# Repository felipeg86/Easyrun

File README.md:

# Easyrun :bike:

Sistema de automatización de préstamo de bicicletas dentro del campus de la Universidad Nacional de Colombia, incorporando la conexión entre estaciones y facilitando el proceso que a la fecha se implementa. El sistema tiene como objetivo principal, reducir los tiempos en el uso del servicio, especialmente en los puntos de prestámo y entrega, además de permitir un control sobre la trazabilidad de cada bicicleta.

Integrantes: 

* Ana Milena Espinosa Jiménez
* Laura Valentina Moreno Castro
* Johan Stevens Higuera Espinel
* Omar Andrés Cely Villate
* Juan Felipe González Pardo
* Kishvari Osorio Delgado
* Johan Sebastian Molina Martinez

## Organización del repositorio

El proyecto se organiza en las sigueintes carpetas:

> * En la carpeta "[Circuit Design](https://github.com/felipeg86/Easyrun/tree/main/Circuit%20Design)" se encuentran las simulaciones, diseños y esquemáticos llevados a cabo en el diseño del hardware del sistema.
> * "[Micropython](https://github.com/felipeg86/Easyrun/tree/main/Micropython)" contiene los scripts utilizados para programar el microcontrolador de la solución.
> * En "[Case Design](https://github.com/felipeg86/Easyrun/tree/main/Case%20Design)" se encuentran los modelos 3D, planos y consideraciones físicas para la cubierta y componentes mecánicos. 
> * "[Budget](https://github.com/felipeg86/Easyrun/tree/main/Budget)" contiene el presupuesto detallado para el desarrollo del prototipo. 
> * "[Imágenes](https://github.com/felipeg86/Easyrun/tree/main/Images)" almacena las imágenes utilizadas en la documentación y en los archivos readme de cada sección.

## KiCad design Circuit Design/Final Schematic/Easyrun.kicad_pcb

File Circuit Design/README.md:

## Organización de la carpeta
### En "[Datasheets](https://github.com/felipeg86/Easyrun/tree/main/Circuit%20Design/Datasheets)" se presentan las hojas de datos y especificaciones de algunos de los componentes de hardware utilizados en la solución.
### "[LTspice Simulations](https://github.com/felipeg86/Easyrun/tree/main/Circuit%20Design/LTspice%20Simulations)" contiene las simulaciones realizadas para el diseño y validación de algunos de los subsistemas.
### "[Final Schematic](https://github.com/felipeg86/Easyrun/tree/main/Circuit%20Design/Final%20Schematic)" almacena los archivos de diseño y fabricación de la placa de circuito impreso del sistema.

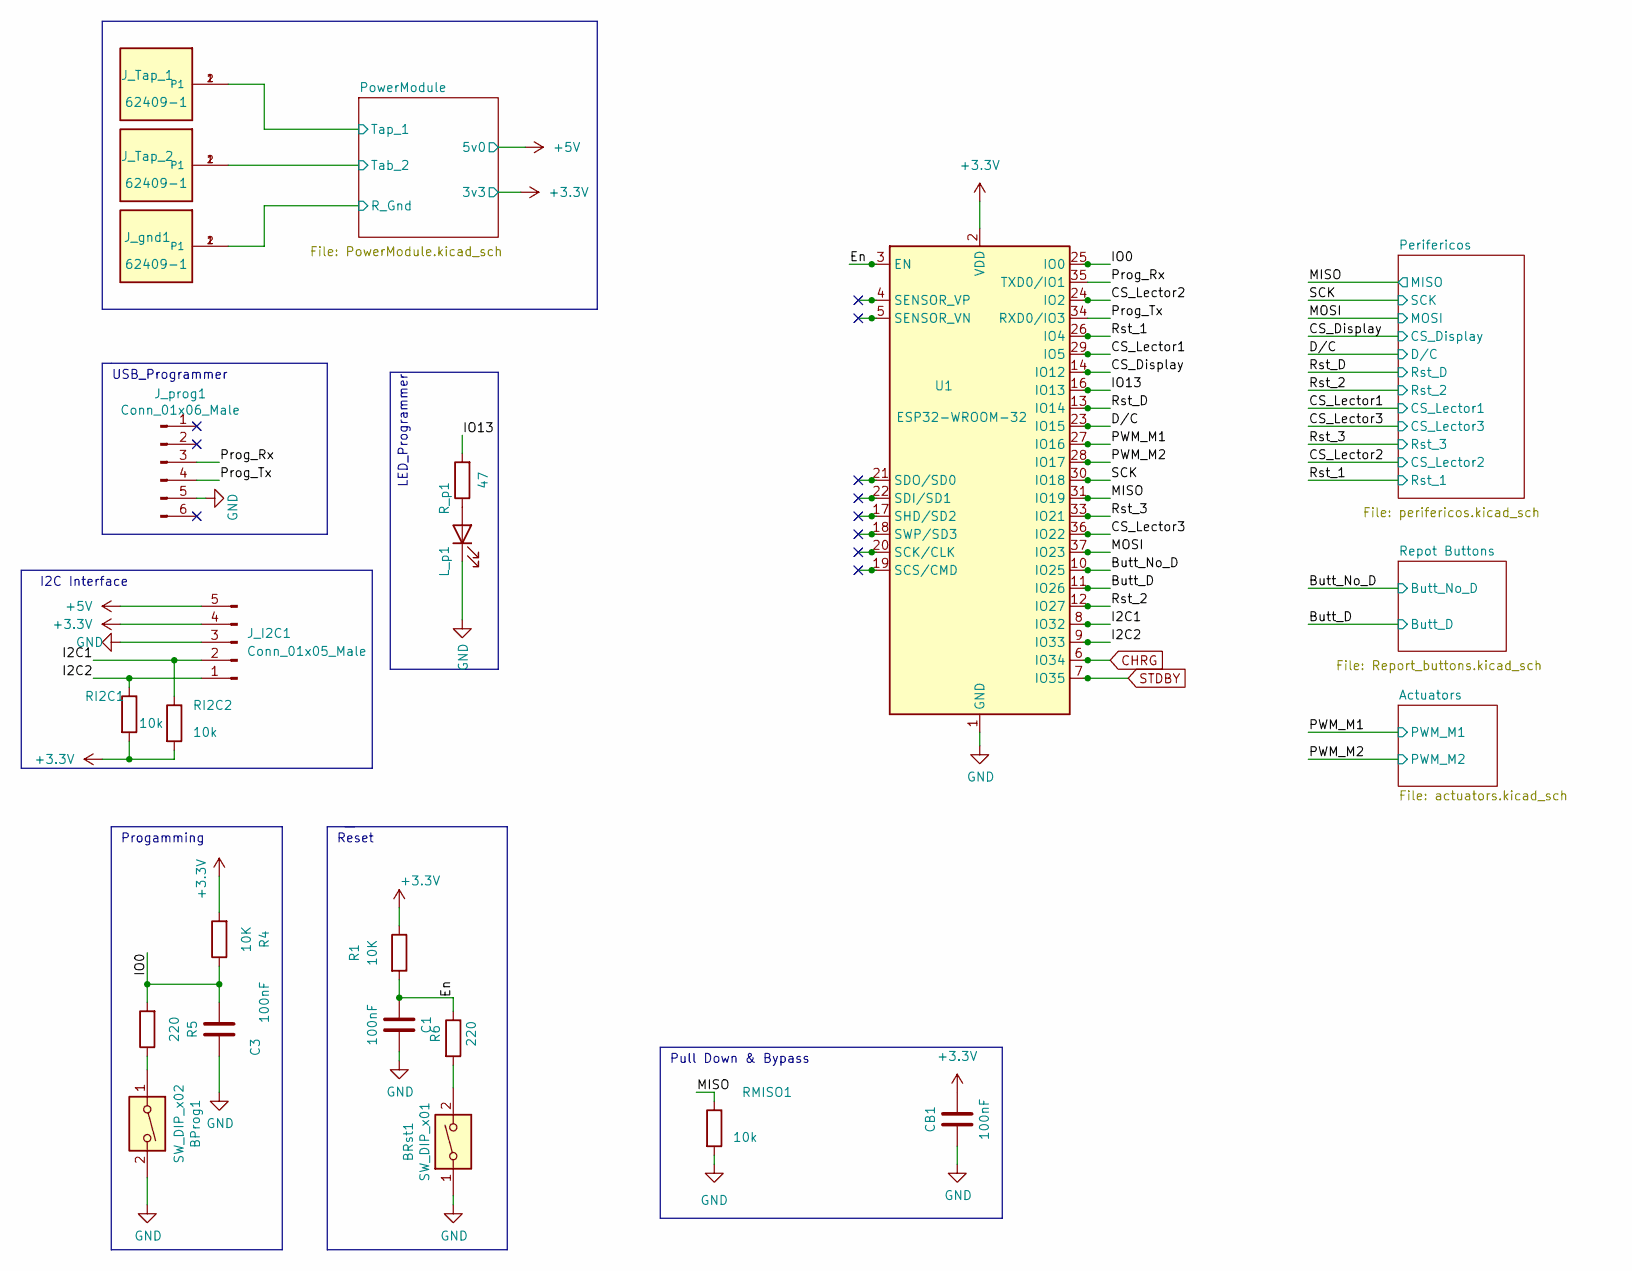
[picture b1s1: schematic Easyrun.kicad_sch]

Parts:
BProg1: SW_DIP_x02; SW_SPST_CK_RS282G05A3
BRst1: SW_DIP_x01; SW_SPST_CK_RS282G05A3
C1, C3: 100nF; C_0805_2012Metric_Pad1.18x1.45mm_HandSolder
CB1: 100nF; C_0805_2012Metric_Pad1.18x1.45mm_HandSolder
J_I2C1: Conn_01x05_Male; PinSocket_1x05_P2.54mm_Horizontal
J_Tap_1, J_Tap_2: 62409-1; TE_62409-1
J_gnd1: 62409-1; TE_62409-1
J_prog1: Conn_01x06_Male; PinHeader_1x06_P2.54mm_Horizontal
L_p1: LED; LED_0805_2012Metric_Pad1.15x1.40mm_HandSolder
R1, R4: 10K; R_0805_2012Metric_Pad1.20x1.40mm_HandSolder
R5, R6: 220; R_0805_2012Metric_Pad1.20x1.40mm_HandSolder
RI2C1, RI2C2: 10k; R_0805_2012Metric_Pad1.20x1.40mm_HandSolder
RMISO1: 10k; R_0805_2012Metric_Pad1.20x1.40mm_HandSolder
R_p1: 47; R_0805_2012Metric_Pad1.20x1.40mm_HandSolder
U1: ESP32-WROOM-32

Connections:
+3V3: CB1.1, J_I2C1.4, R1.1, R4.2, RI2C1.2, RI2C2.2, U1.2 (VDD); also elsewhere on the board
+5V: J_I2C1.5; also elsewhere on the board
/Butt_D: U1.11 (IO26); also elsewhere on the board
/Butt_No_D: U1.10 (IO25); also elsewhere on the board
/CS_Display: U1.14 (IO12); also elsewhere on the board
/CS_Lector1: U1.29 (IO5); also elsewhere on the board
/CS_Lector2: U1.24 (IO2); also elsewhere on the board
/CS_Lector3: U1.36 (IO22); also elsewhere on the board
/D/C: U1.23 (IO15); also elsewhere on the board
/En: C1.2, R1.2, R6.1, U1.3 (EN)
/I2C1: J_I2C1.2, RI2C2.1, U1.8 (IO32)
/I2C2: J_I2C1.1, RI2C1.1, U1.9 (IO33)
/IO0: C3.1, R4.1, R5.2, U1.25 (IO0)
/IO13: R_p1.2, U1.16 (IO13)
/MISO: RMISO1.1, U1.31 (IO19); also elsewhere on the board
/MOSI: U1.37 (IO23); also elsewhere on the board
/PWM_M1: U1.27 (IO16); also elsewhere on the board
/PWM_M2: U1.28 (IO17); also elsewhere on the board
/PowerModule/R_Gnd: J_gnd1.1, J_gnd1.2 (P1); also elsewhere on the board
/PowerModule/Tab_2: J_Tap_2.1, J_Tap_2.2 (P1); also elsewhere on the board
/PowerModule/Tap_1: J_Tap_1.1, J_Tap_1.2 (P1); also elsewhere on the board
/Prog_Rx: J_prog1.3, U1.35 (TXD0/IO1)
/Prog_Tx: J_prog1.4, U1.34 (RXD0/IO3)
/Rst_1: U1.26 (IO4); also elsewhere on the board
/Rst_2: U1.12 (IO27); also elsewhere on the board
/Rst_3: U1.33 (IO21); also elsewhere on the board
/Rst_D: U1.13 (IO14); also elsewhere on the board
/SCK: U1.30 (IO18); also elsewhere on the board
CHRG: U1.6 (IO34); also elsewhere on the board
GND: BProg1.2, BRst1.1, C1.1, C3.2, CB1.2, J_I2C1.3, J_prog1.5, L_p1.1 (K), RMISO1.2, U1.1 (GND), U1.15 (GND), U1.38 (GND), U1.39 (GND); also elsewhere on the board
unnamed: BProg1.1, R5.1
unnamed: BRst1.2, R6.2
unnamed: L_p1.2 (A), R_p1.1
STDBY: U1.7 (IO35); also elsewhere on the board

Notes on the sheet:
LED_Programmer
I2C Interface
Progamming
Pull Down & Bypass
Reset
USB_Programmer

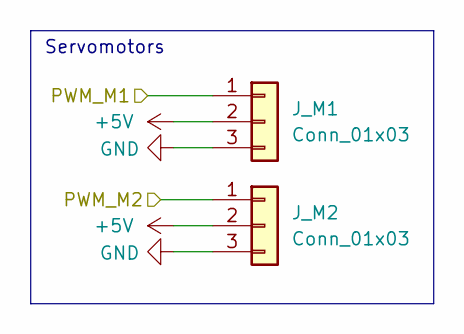
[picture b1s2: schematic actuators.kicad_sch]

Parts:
J_M1, J_M2: Conn_01x03; JST_EH_S3B-EH_1x03_P2.50mm_Horizontal

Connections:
+5V: J_M1.2, J_M2.2; also elsewhere on the board
/PWM_M1: J_M1.1; also elsewhere on the board
/PWM_M2: J_M2.1; also elsewhere on the board
GND: J_M1.3, J_M2.3; also elsewhere on the board

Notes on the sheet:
Servomotors

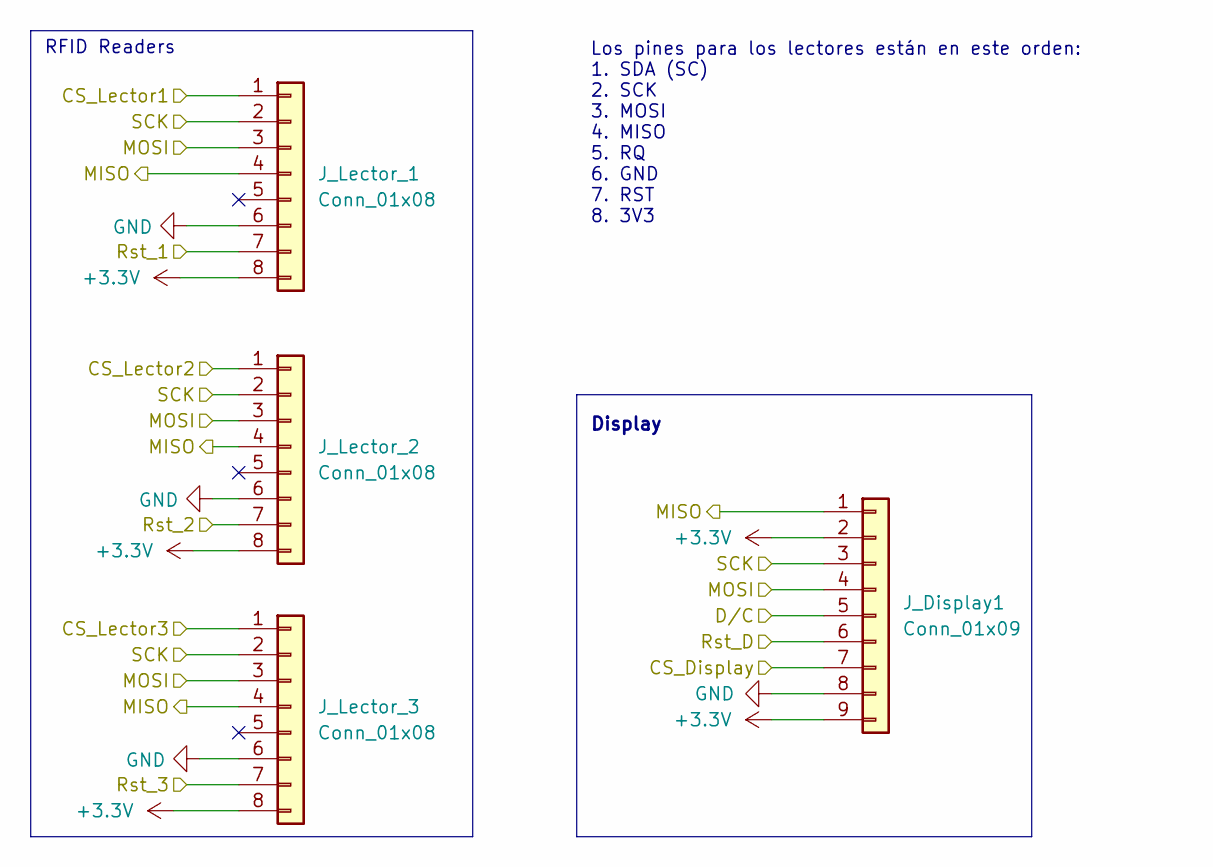
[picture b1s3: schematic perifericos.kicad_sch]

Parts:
J_Display1: Conn_01x09; JST_EH_S9B-EH_1x09_P2.50mm_Horizontal
J_Lector_1, J_Lector_2, J_Lector_3: Conn_01x08; JST_EH_S8B-EH_1x08_P2.50mm_Horizontal

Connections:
+3V3: J_Display1.2, J_Display1.9, J_Lector_1.8, J_Lector_2.8, J_Lector_3.8; also elsewhere on the board
/CS_Display: J_Display1.7; also elsewhere on the board
/CS_Lector1: J_Lector_1.1; also elsewhere on the board
/CS_Lector2: J_Lector_2.1; also elsewhere on the board
/CS_Lector3: J_Lector_3.1; also elsewhere on the board
/D/C: J_Display1.5; also elsewhere on the board
/MISO: J_Display1.1, J_Lector_1.4, J_Lector_2.4, J_Lector_3.4; also elsewhere on the board
/MOSI: J_Display1.4, J_Lector_1.3, J_Lector_2.3, J_Lector_3.3; also elsewhere on the board
/Rst_1: J_Lector_1.7; also elsewhere on the board
/Rst_2: J_Lector_2.7; also elsewhere on the board
/Rst_3: J_Lector_3.7; also elsewhere on the board
/Rst_D: J_Display1.6; also elsewhere on the board
/SCK: J_Display1.3, J_Lector_1.2, J_Lector_2.2, J_Lector_3.2; also elsewhere on the board
GND: J_Display1.8, J_Lector_1.6, J_Lector_2.6, J_Lector_3.6; also elsewhere on the board

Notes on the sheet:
RFID Readers
Display
Los pines para los lectores están en este orden: 1. SDA (SC) 2. SCK 3. MOSI 4. MISO 5. RQ 6. GND 7. RST 8. 3V3

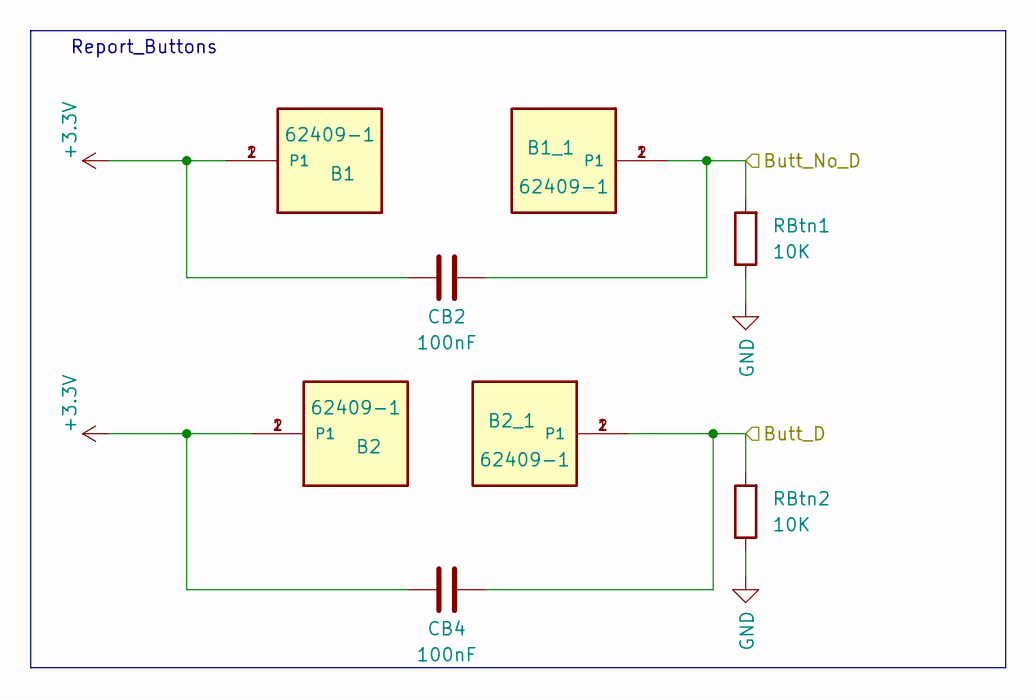
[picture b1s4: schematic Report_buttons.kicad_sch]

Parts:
B1, B1_1, B2, B2_1: 62409-1; TE_62409-1
CB2, CB4: 100nF; C_0805_2012Metric_Pad1.18x1.45mm_HandSolder
RBtn1, RBtn2: 10K; R_0805_2012Metric_Pad1.20x1.40mm_HandSolder

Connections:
+3V3: B1.1, B1.2 (P1), B2.1, B2.2 (P1), CB2.1, CB4.1; also elsewhere on the board
/Butt_D: B2_1.1, B2_1.2 (P1), CB4.2, RBtn2.2; also elsewhere on the board
/Butt_No_D: B1_1.1, B1_1.2 (P1), CB2.2, RBtn1.2; also elsewhere on the board
GND: RBtn1.1, RBtn2.1; also elsewhere on the board

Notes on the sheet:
Report_Buttons

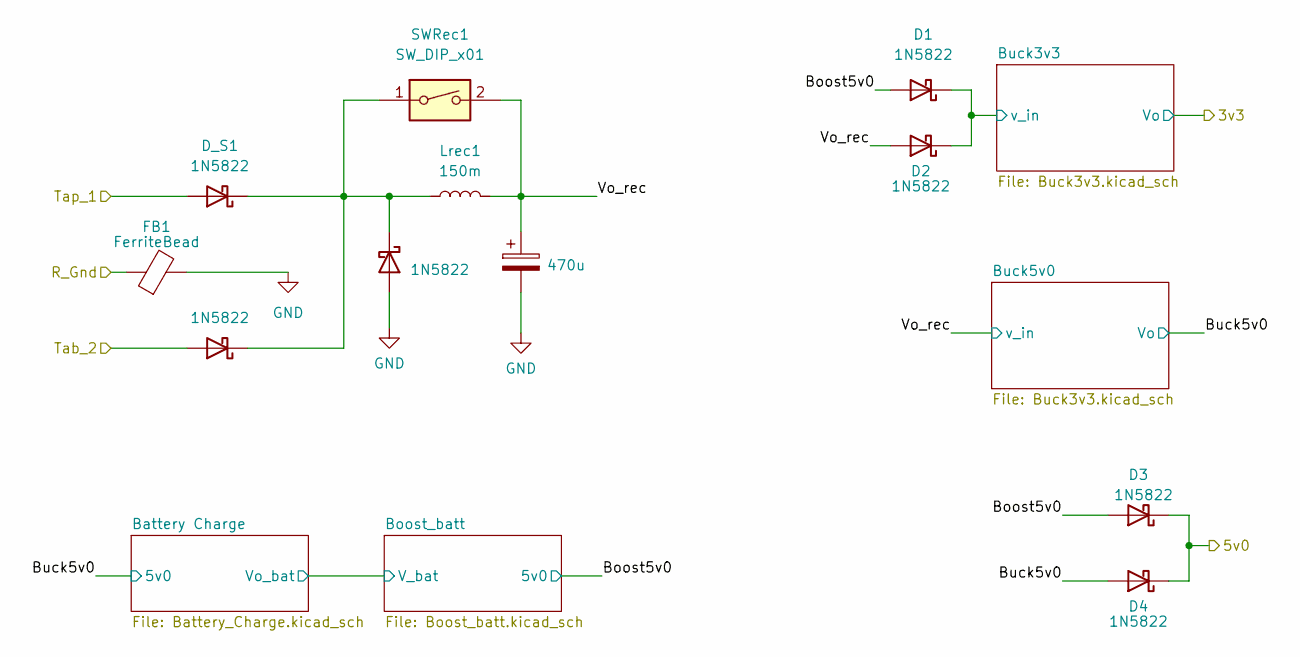
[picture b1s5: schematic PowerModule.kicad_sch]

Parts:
Crec1: 470u; CP_Radial_D6.3mm_P2.50mm
D1, D2, D3, D4: 1N5822; D_DO-201AE_P5.08mm_Vertical_AnodeUp
DFly1: 1N5822; D_DO-201AE_P5.08mm_Vertical_AnodeUp
D_S1, D_S2: 1N5822; D_DO-201AE_P5.08mm_Vertical_AnodeUp
FB1: FerriteBead; R_1812_4532Metric_Pad1.30x3.40mm_HandSolder
Lrec1: 150m; L_Toroid_Vertical_L25.4mm_W14.7mm_P12.20mm_Vishay_TJ5_BigPa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
SWRec1: SW_DIP_x01; PinHeader_1x02_P2.54mm_Vertical_SMD_Pin1Left

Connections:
+5V: D3.1 (K), D4.1 (K); also elsewhere on the board
/PowerModule/Boost5v0: D1.2 (A), D3.2 (A); also elsewhere on the board
/PowerModule/Buck3v3/v_in: D1.1 (K), D2.1 (K); also elsewhere on the board
/PowerModule/Buck5v0: D4.2 (A); also elsewhere on the board
/PowerModule/R_Gnd: FB1.1; also elsewhere on the board
/PowerModule/Tab_2: D_S2.2 (A); also elsewhere on the board
/PowerModule/Tap_1: D_S1.2 (A); also elsewhere on the board
/PowerModule/Vo_rec: Crec1.1, D2.2 (A), Lrec1.2, SWRec1.2; also elsewhere on the board
GND: Crec1.2, DFly1.2 (A), FB1.2; also elsewhere on the board
unnamed: DFly1.1 (K), D_S1.1 (K), D_S2.1 (K), Lrec1.1, SWRec1.1

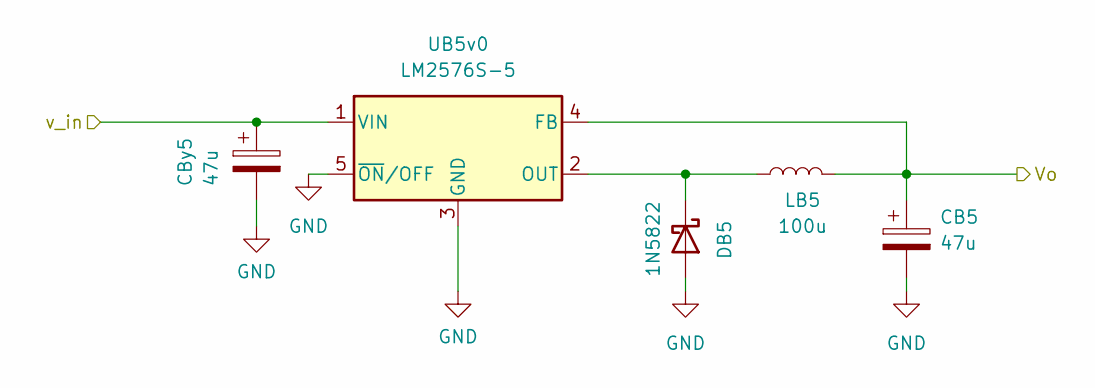
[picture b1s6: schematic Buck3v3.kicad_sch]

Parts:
CB5: 47u; CP_Elec_6.3x5.8
CBy5: 47u; CP_EIA-7343-43_Kemet-X_Pad2.25x2.55mm_HandSolder
DB5: 1N5822; D_DO-201AE_P5.08mm_Vertical_AnodeUp
LB5: 100u; L_Toroid_Vertical_L25.4mm_W14.7mm_P12.20mm_Vishay_TJ5_BigPa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
UB5v0: LM2576S-5; TO-263-5_TabPin3

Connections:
/PowerModule/Buck5v0: CB5.1, LB5.2, UB5v0.4 (FB); also elsewhere on the board
/PowerModule/Vo_rec: CBy5.1, UB5v0.1 (VIN); also elsewhere on the board
GND: CB5.2, CBy5.2, DB5.2 (A), UB5v0.3 (GND), UB5v0.5 (~ON/OFF); also elsewhere on the board
unnamed: DB5.1 (K), LB5.1, UB5v0.2 (OUT)

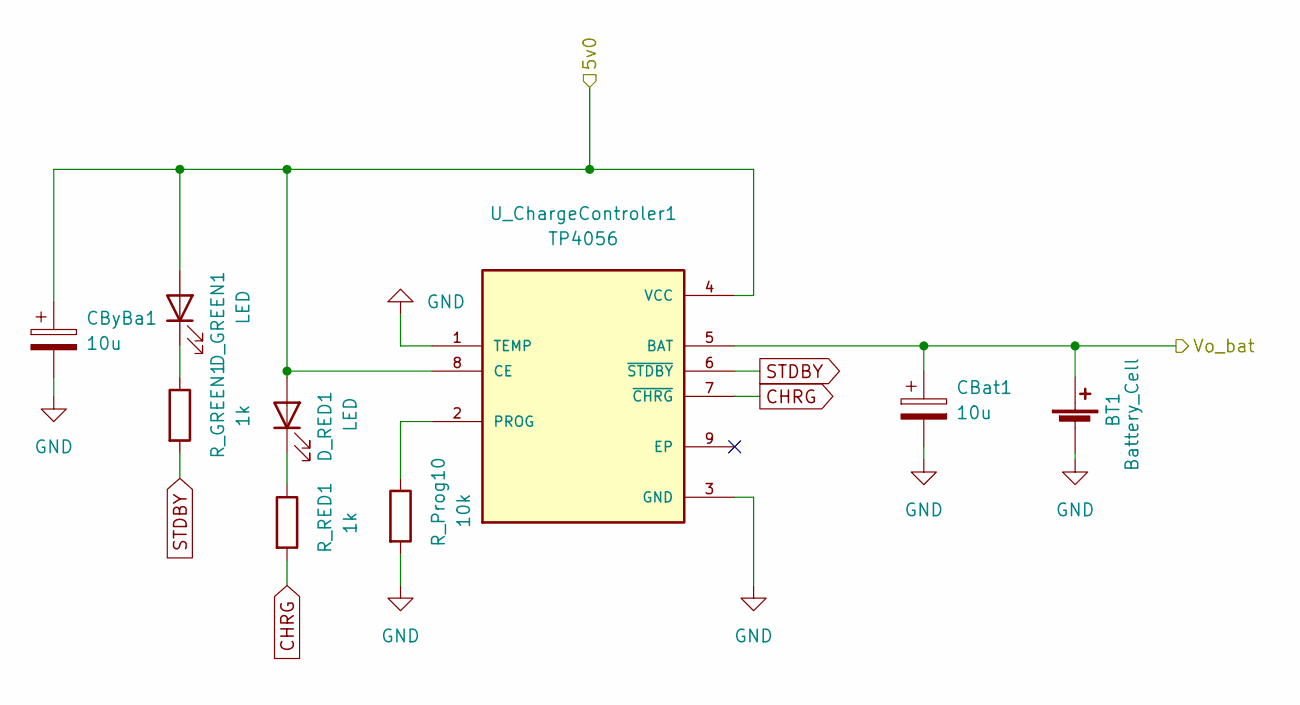
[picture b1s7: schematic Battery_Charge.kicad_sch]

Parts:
BT1: Battery_Cell; BatteryHolder_MPD_BH-18650-PC2
CBat1: 10u; CP_Elec_6.3x5.8
CByBa1: 10u; CP_Elec_6.3x5.8
D_GREEN1: LED; LED_0805_2012Metric_Pad1.15x1.40mm_HandSolder
D_RED1: LED; LED_0805_2012Metric_Pad1.15x1.40mm_HandSolder
R_GREEN1: 1k; R_0805_2012Metric_Pad1.20x1.40mm_HandSolder
R_Prog10: 10k; R_0805_2012Metric_Pad1.20x1.40mm_HandSolder
R_RED1: 1k; R_0805_2012Metric_Pad1.20x1.40mm_HandSolder
U_ChargeControler1: TP4056; SOP127P600X175-9N

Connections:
/PowerModule/Battery Charge/Vo_bat: BT1.1 (+), CBat1.1, U_ChargeControler1.5 (BAT); also elsewhere on the board
/PowerModule/Buck5v0: CByBa1.1, D_GREEN1.2 (A), D_RED1.2 (A), U_ChargeControler1.4 (VCC), U_ChargeControler1.8 (CE); also elsewhere on the board
CHRG: R_RED1.2, U_ChargeControler1.7 (~CHRG); also elsewhere on the board
GND: BT1.2 (-), CBat1.2, CByBa1.2, R_Prog10.2, U_ChargeControler1.1 (TEMP), U_ChargeControler1.3 (GND); also elsewhere on the board
unnamed: D_GREEN1.1 (K), R_GREEN1.1
unnamed: D_RED1.1 (K), R_RED1.1
unnamed: R_Prog10.1, U_ChargeControler1.2 (PROG)
STDBY: R_GREEN1.2, U_ChargeControler1.6 (~STDBY); also elsewhere on the board

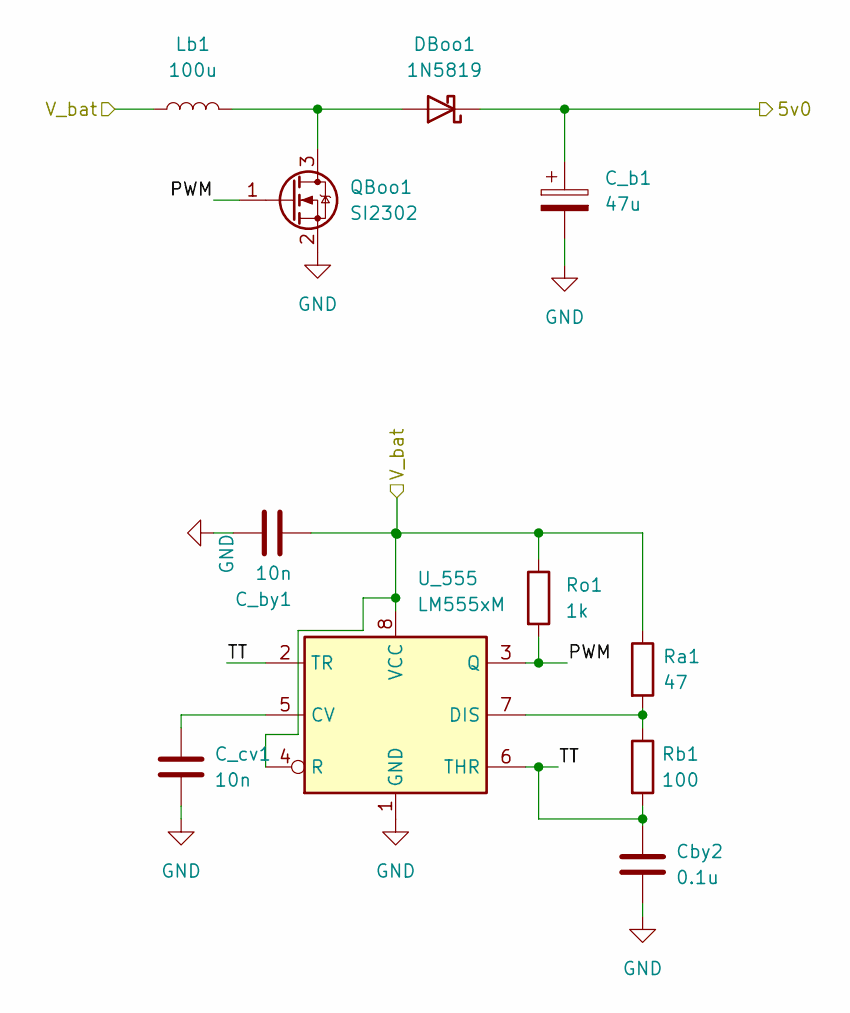
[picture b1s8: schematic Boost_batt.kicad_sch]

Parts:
C_b1: 47u; CP_Elec_6.3x5.8
C_by1: 10n; C_0805_2012Metric_Pad1.18x1.45mm_HandSolder
C_cv1: 10n; C_0805_2012Metric_Pad1.18x1.45mm_HandSolder
Cby2: 0.1u; C_0805_2012Metric_Pad1.18x1.45mm_HandSolder
DBoo1: 1N5819; D_DO-201AE_P5.08mm_Vertical_AnodeUp
Lb1: 100u; L_Toroid_Vertical_L25.4mm_W14.7mm_P12.20mm_Vishay_TJ5_BigPa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
QBoo1: SI2302; SOT-23
Ra1: 47; R_0805_2012Metric_Pad1.20x1.40mm_HandSolder
Rb1: 100; R_0805_2012Metric_Pad1.20x1.40mm_HandSolder
Ro1: 1k; R_0805_2012Metric_Pad1.20x1.40mm_HandSolder
U_555: LM555xM; SOIC-8_3.9x4.9mm_P1.27mm

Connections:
/PowerModule/Battery Charge/Vo_bat: Lb1.1; also elsewhere on the board
/PowerModule/Boost5v0: C_b1.1, DBoo1.1 (K); also elsewhere on the board
/PowerModule/Boost_batt/PWM: QBoo1.1 (G), Ro1.2, U_555.3 (Q)
/PowerModule/Boost_batt/TT: Cby2.1, Rb1.2, U_555.2 (TR), U_555.6 (THR)
GND: C_b1.2, C_by1.1, C_cv1.2, Cby2.2, QBoo1.2 (S), U_555.1 (GND); also elsewhere on the board
unnamed: C_by1.2, Ra1.1, Ro1.1, U_555.4 (R), U_555.8 (VCC)
unnamed: C_cv1.1, U_555.5 (CV)
unnamed: DBoo1.2 (A), Lb1.2, QBoo1.3 (D)
unnamed: Ra1.2, Rb1.1, U_555.7 (DIS)

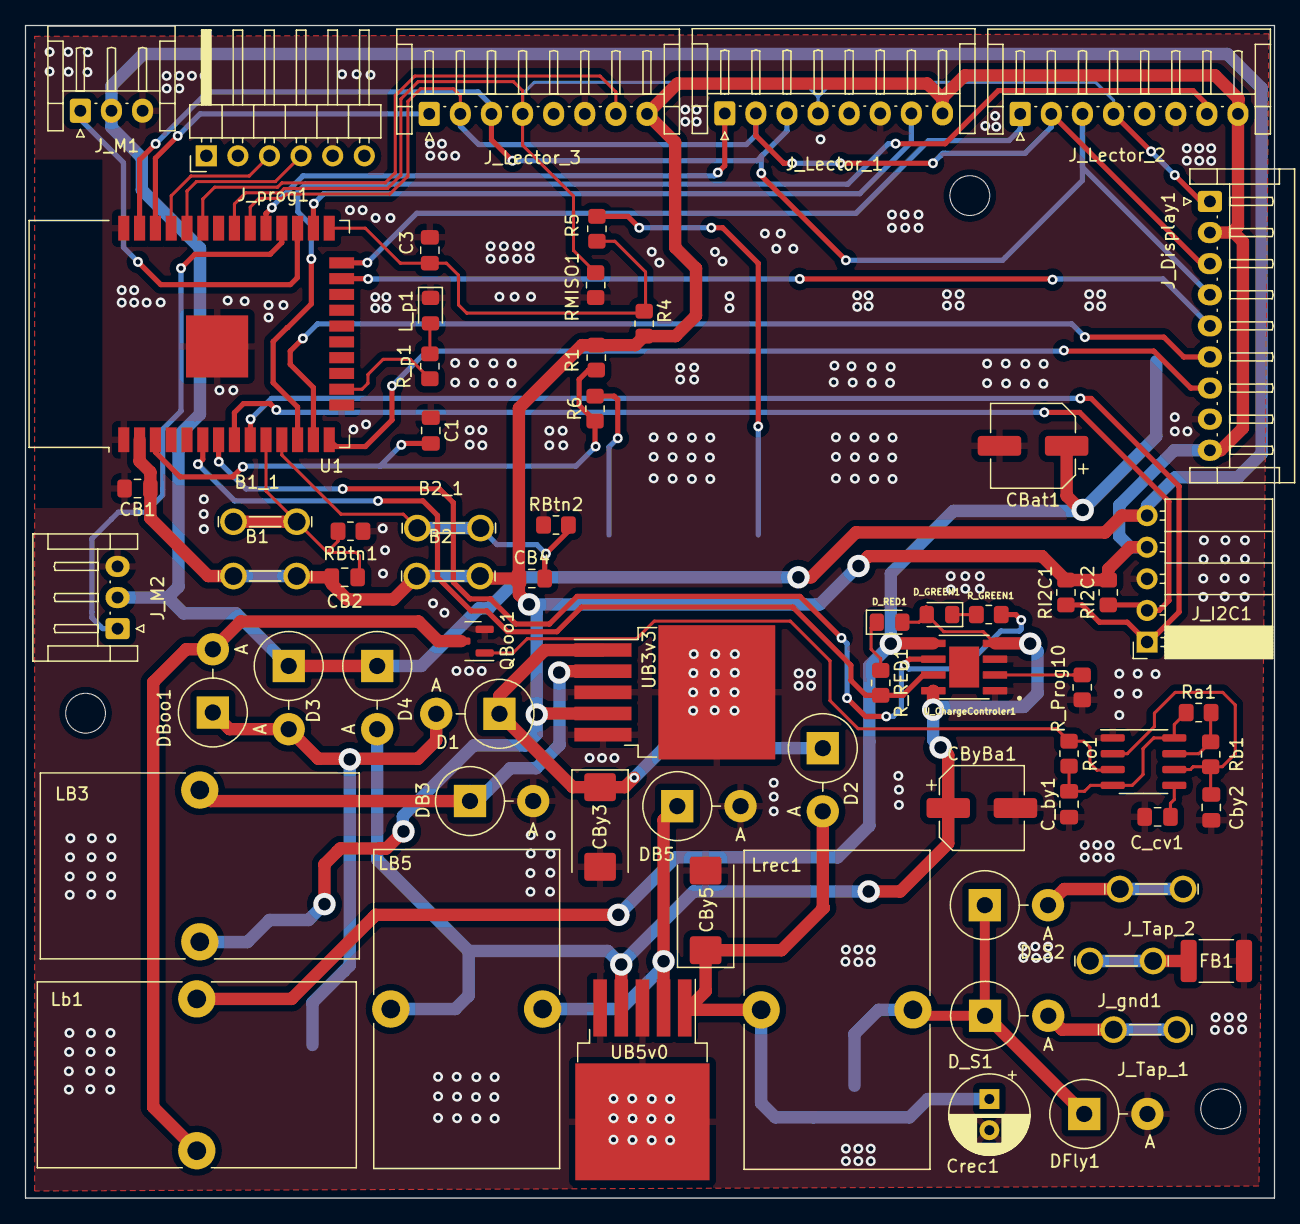
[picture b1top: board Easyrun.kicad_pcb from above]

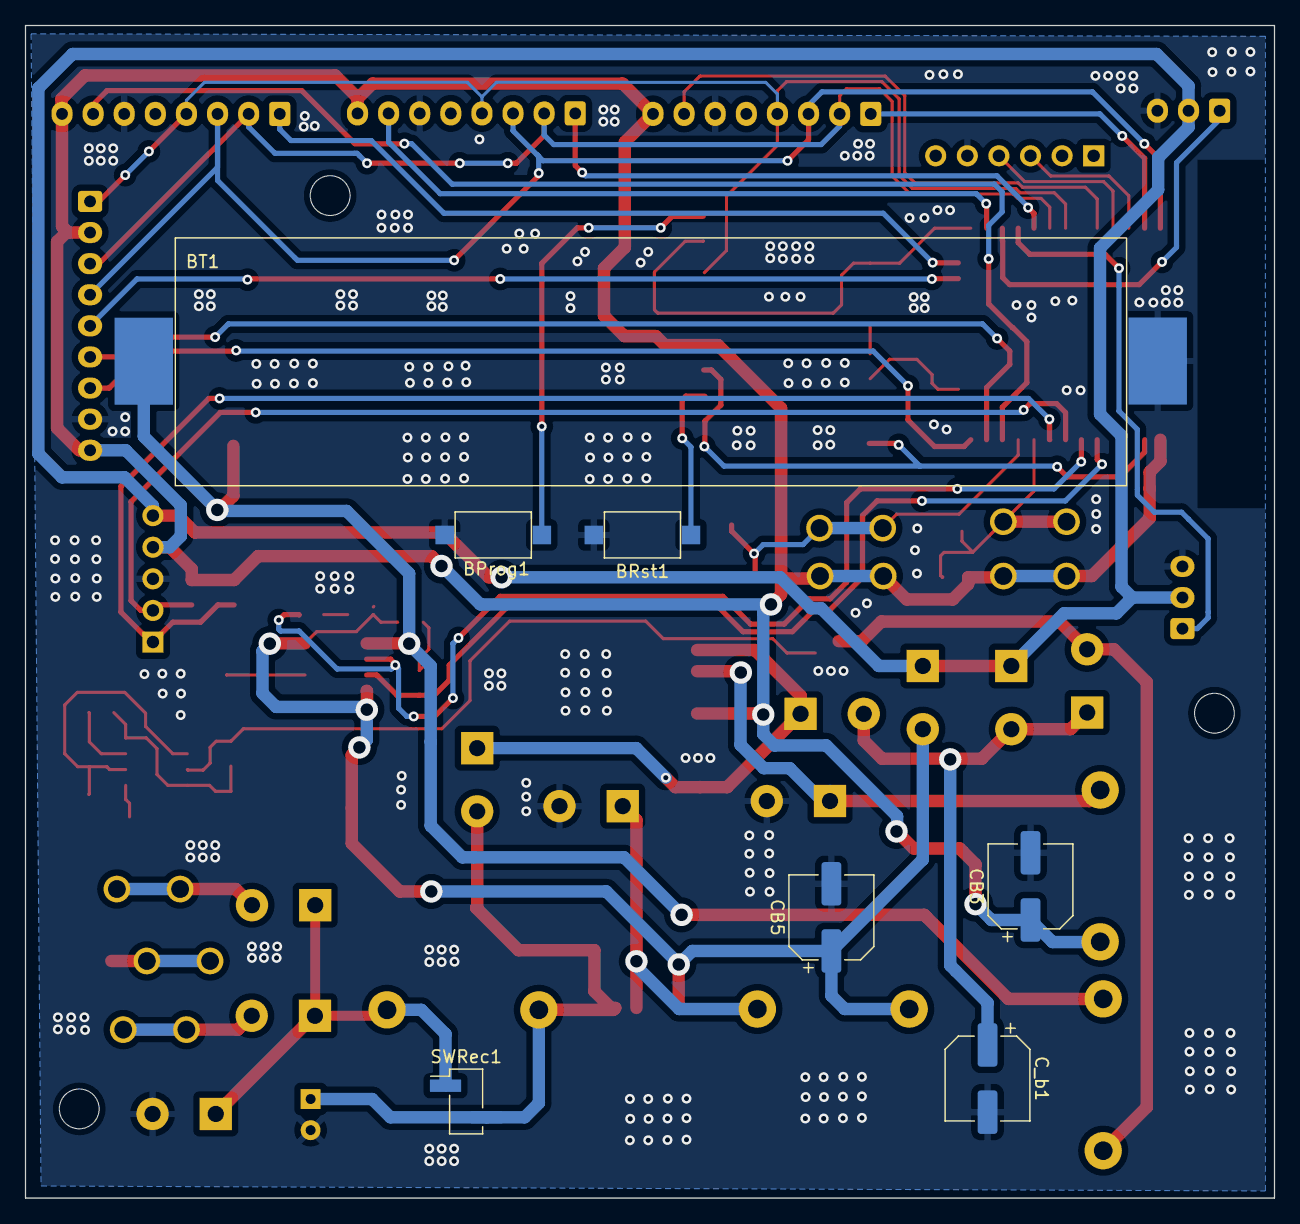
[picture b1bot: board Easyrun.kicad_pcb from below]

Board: 2 copper layers, 100.4 x 94.2 mm, 75 parts (7 on the bottom side), 51 nets.

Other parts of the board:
CB3: 47u; CP_Elec_6.3x5.8
CBy3: 47u; CP_EIA-7343-43_Kemet-X_Pad2.25x2.55mm_HandSolder
DB3: 1N5822; D_DO-201AE_P5.08mm_Vertical_AnodeUp
LB3: 100u; L_Toroid_Vertical_L25.4mm_W14.7mm_P12.20mm_Vishay_TJ5_BigPa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
UB3v3: LM2576S-5; TO-263-5_TabPin3

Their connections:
+3V3: CB3.1, LB3.2, UB3v3.4 (FB); also elsewhere on the board
/PowerModule/Buck3v3/v_in: CBy3.1, UB3v3.1 (VIN); also elsewhere on the board
GND: CB3.2, CBy3.2, DB3.2 (A), UB3v3.3 (GND), UB3v3.5 (~ON/OFF); also elsewhere on the board
unnamed: DB3.1 (K), LB3.1, UB3v3.2 (OUT)

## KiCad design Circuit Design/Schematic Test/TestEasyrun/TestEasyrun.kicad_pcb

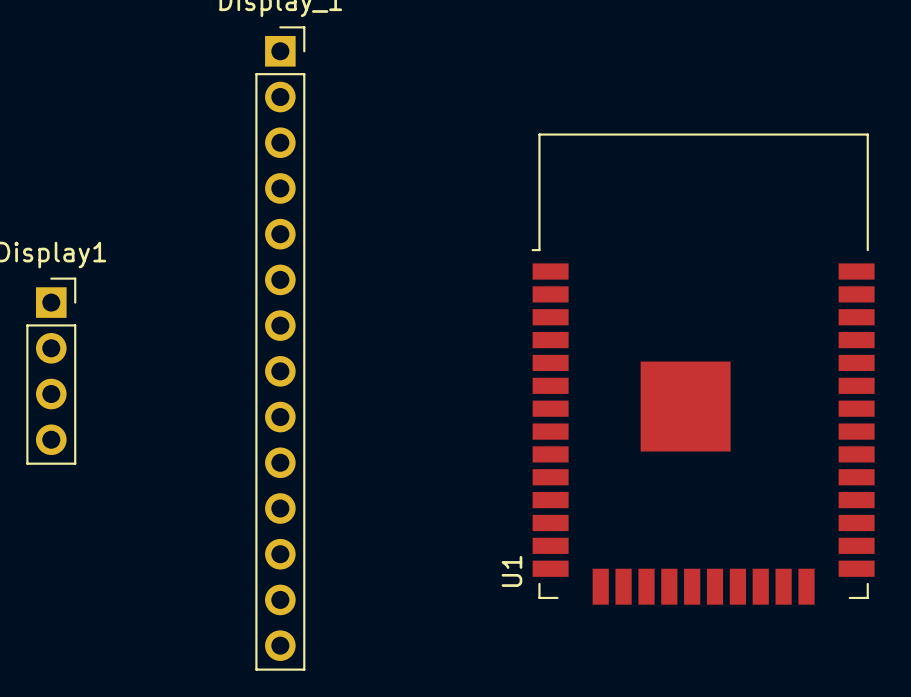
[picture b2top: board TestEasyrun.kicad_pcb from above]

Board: 2 copper layers, 3 parts (0 on the bottom side), 8 nets, no tracks yet.

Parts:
Display1: Conn_01x04_Female; PinSocket_1x04_P2.54mm_Vertical
Display_1: Conn_01x14_Female; PinSocket_1x14_P2.54mm_Vertical
U1: ESP32-WROOM-32

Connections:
/3v3: Display_1.7, Display_1.14
CS_Display: Display_1.12, U1.23 (IO15)
D/C: Display_1.10, U1.7 (IO35)
GND: Display_1.13, U1.1 (GND), U1.15 (GND), U1.38 (GND), U1.39 (GND)
MISO: Display_1.6, U1.31 (IO19)
MOSI: Display_1.9, U1.37 (IO23)
Rst_D: Display_1.11, U1.6 (IO34)
SCK: Display_1.8, U1.30 (IO18)

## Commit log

2022-04-15 Minor Changes
2022-04-18 Add files via upload
    Simulaciones previas, sistema de alimentación completo
2022-04-19 Diagrama de despliegue agregado
2022-04-19 Diagrama de componentes agregado al read.me
2022-04-27 Add files via upload
    Presupuesto del proyecto, componentes
2022-04-27 Add files via upload
    Simulación del circuito de potencia para la alimentación
2022-04-28 ESP changed
2022-04-28 Pruebita
    Puse un archivo ...
2022-04-28 Prueba2
2022-04-28 Borro pruebita
2022-04-29 Some changes on Power Controller
2022-04-29 Esquema Lectores
    Se agregan las conexiones de los 3 lectores en el esquemático
2022-04-30 I forgot what else I did uwu't
2022-05-03 Changes in mqtt comunnication
    First probe of mqtt connection. Here I try to connect the ESP32 with my computer like host
2022-05-03 Motor Schematic
    Se incluye el esquemático del motor junto con algunas funciones, como condensador de bypass y elementos de antirrebote
2022-05-03 Arreglo de Esquemático Lectores
    Se arregló el esquemático de los lectores, utilizando etiquetas para las conexiones
2022-05-04 I2C interface added
2022-05-04 Botones de reporte
    Se agregan los botones de reporte y se determinan los puertos que no serán utilizados
2022-05-05 Arreglo I2C
    Se ponen junto a la interfaz I2C pines de alimentación que se podrán utilizar según las necesidades observadas
2022-05-05 Added some controller files
2022-05-05 Feedback triangular signal resistor modified
2022-05-05 Nothing really'
2022-05-06 New controller
2022-05-07 todo mal
2022-05-07 New controller almost working
2022-05-07 Lectores
    Esquematico lectores
2022-05-07 EsquematicoSinCircuitoPot
2022-05-07 Huellas sin botones ni potencia
2022-05-08 Power integration
    Power integration
2022-05-08 New rectifier simulation
2022-05-08 Controllers
2022-05-09 Gate driver tests
2022-05-09 3v3 Controller fixed
2022-05-10 Old gate driver removed, looking for something else
2022-05-10 Footprints added and new drivers designed
2022-05-10 Almost all footprints added
2022-05-10 Controller simmulation removed
2022-05-10 PWM generator file
2022-05-10 Botón de rst
    Se arreglaron las resistencias del botón de reset y enable
2022-05-10 Include the battery power module
2022-05-10 Change the global labels
2022-05-10 Ready to merge
2022-05-10 Nothing
2022-05-10 Add conection changes
    Add conection changes, using different types of hierarchien
2022-05-12 Labels
2022-05-13 Old schematic version deleted
2022-05-14 Some stuff deleted
2022-05-14 JUst the backup
2022-05-14 Power Factor of Rectifier almost fixed
2022-05-14 Rectifier almost ready. Issues with current phase
2022-05-14 LM2576S model added
2022-05-14 Power Module on schematic almost ready
2022-05-14 Rprog changed
2022-05-14 Footprints
2022-05-14 Manufacturer specs taken into account for bucks
2022-05-14 Ferrite bead added
2022-05-14 Boost
2022-05-14 Organización PCB
2022-05-14 Organización de PCB 2.0
    Se organizaron los componentes de la PCB
2022-05-15 Mejor ruteo xd Felipe cambie las huellas
2022-05-15 PCB distribution
2022-05-15 More free space schematic
2022-05-15 Just a backup
2022-05-16 Ruteo PCB
    Se agregó el archivo Easyrun_autoroute, con el ruteo de la PCB basado en autoroute :v
2022-05-16 Mounting holes
2022-05-16 Cambio orden pines lectores y display
    Se cambiaron para facilitar el ruteo.
2022-05-17 PCB almost ready
2022-05-17 Final
2022-05-17 Ruteo de PCB
    Se agregó el ruteo de la PCB verificando las conexiones
2022-05-17 Corrección tamaño de vías
    Se corrigió el tamaño de las vías pasantes de la PCB
2022-05-19 Nothing, I guess
2022-05-19 Pretty much nothing
2022-05-20 Gerber files were generated
2022-05-20 Cambio pines CS y Rst Display
    Se cambiaron los pines CS y Rst del Display que estaban en pines solo entrada de la ESP, por los pines STDBY y CHRG de la parte de potencia
2022-05-20 Archivos gerber y de taladro
2022-05-24 List of components generated
2022-05-25 MQTT works with dictionaries! uwu
2022-05-28 Some tests
2022-05-29 prueba con json y perifericos
    se hizo una prueba para el uso de archivos Json y un código prueba para el inicio del código de los perifericos
2022-05-29 codigo
2022-05-30 Correcion del archivo de perifericos y algunas clases
    Se modifico el archivo de perifericos por un código basada en if else anidados
2022-05-30 Just some cleanup uwu
2022-05-30 New rectifier topology
2022-05-30 Changed some values on the schematic. Doesn't affect PCB
2022-05-30 Updated values on PCB
2022-05-31 Initial power factor verified
2022-05-31 Initial efficiency also verified
2022-05-31 New transformer
2022-05-31 Adición de pruebas con display y micropython
2022-06-03 Budget almost ready
2022-06-03 The budget is ready i think
2022-06-04 Actualización del presupuesto
    Se actualizó el presupuesto con los conectores JST necesarios para el proyecto
2022-06-04 Buck converters simmulations
2022-06-04 Unsuccesful attempt of a full power module simmulation
2022-06-04 Some formating in the budget
2022-06-04 Budget updated
2022-06-05 Avances Programación
    Se avanzó en el flujo de programación de préstamo
2022-06-06 Se agregan imágenes para la wiki
2022-06-06 Se realizaron arreglos en las clases creadas
2022-06-07 Simulation Boost
2022-06-07 Mas imagenes :v:
2022-06-07 Funcion servo y asignacion datos de persona
    Se crearon las funciones para abrir y cerrar el seguro mecanico. Se avanzo en la asignacion de datos de la persona en el proceso de prestamo.
2022-06-07 Más imágenes para la documentación
2022-06-07 Add images for wiki
2022-06-07 Code changes
    Add SI2 functioning and the Prestamo.json file
2022-06-07 more changes
2022-06-08 Se agrega el código de esqueleto
    Se completa el código expresado en los diagramas de de flujo; Aún hacen falta la integración de la pantalla, los botones y la creación de interrupciones
2022-06-08 Un código más cortico :v
2022-06-09 MyDisplay class construction and printText method tested
2022-06-09 Making printText function. printShortText function done
2022-06-10 Función de prueba del display
    Se agrega un código de prueba del display con el cual se verificó la funcionalidad del código, integrando lectores y display
2022-06-11 cambios pequeños
2022-06-11 MQTT, source identification
    The system can identified the source of the message, so it is simple to classificate the message
2022-06-11 Messages
    Information that we will send from the ESP
2022-06-11 Messages function integration
    Integration of the function that integrated the message with the main code
2022-06-12 mas cambios bobos :v
2022-06-12 pruebas interrupciones
2022-06-13 Interrupciones y ajustes para comunicaciones
    Se agregaron las 4 interrupciones para el sistema, se cambiaron y agregaron plantillas json para recibir y enviar datos al sistema de información y se cambiaron las clases del sistema, para eliminar 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
2022-06-13 Código casi final
2022-06-14 Text function completed and UN logo added
2022-06-14 Image to RGB565 raw file added
2022-06-15 Más cambios pequeños
2022-06-16 Codigo verificado
    Se agrega el código completo, con las pruebas de verificación para las partes; Falta ingresar la parte de comunicación en el código y utilizar la función de la pantalla final
2022-06-20 Intregation MQTT comunication
2022-06-21 Actualización de la función del display
2022-06-22 Compra de CP2102
2022-06-26 cambios pequeños x3674
2022-07-02 Last Display Function
2022-07-03 Pruebas de funcionamiento del sistema
    Se agregaron las pruebas de funcionamiento de Software, componente por componente.
2022-07-03 More videos
2022-07-04 Modification MQTT connection
2022-07-04 Description of the MQTT code
    Description with comments inside the code
2022-07-04 Últimos cambios pequeños
2022-07-04 Final probes MQTT
2022-07-04 Integration
2022-07-05 Connection with SI
2022-07-05 Final Probe with SI
